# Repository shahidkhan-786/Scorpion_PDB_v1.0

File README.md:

# Scorpion_PDB_v1.0

I am making a Buck converter. 
I am making it using a TPS563200 Chip...I used ths because it is Small, Cheap, and Reliable to output 3A Current.

This is my schematic...I mostly referred to DataSheet of TPS563200.

This is the Layout/Routing part...I think this was the hardest part of the project, since the DataSheet gave very strict instructions for this.

Hopefully after soldering all components it look like this.

The sole purpose of the project is to power my Drone...or Future Drone : "Scorpion" ;)

Note : PDB translates to 'Power Distribution Board'

As the name suggests it will disribute power to all my Servo motors, ESC's, ESP32 (which i will be using for my Flight Controller for Scorpion) and/or any other Sensors
that I will be using in future...that's exactly why I have created 7 outputs...!

Here is the BOM of this PDB : 

This is Component Part.

This is PCB Part (I am ordering from JLCPCB).

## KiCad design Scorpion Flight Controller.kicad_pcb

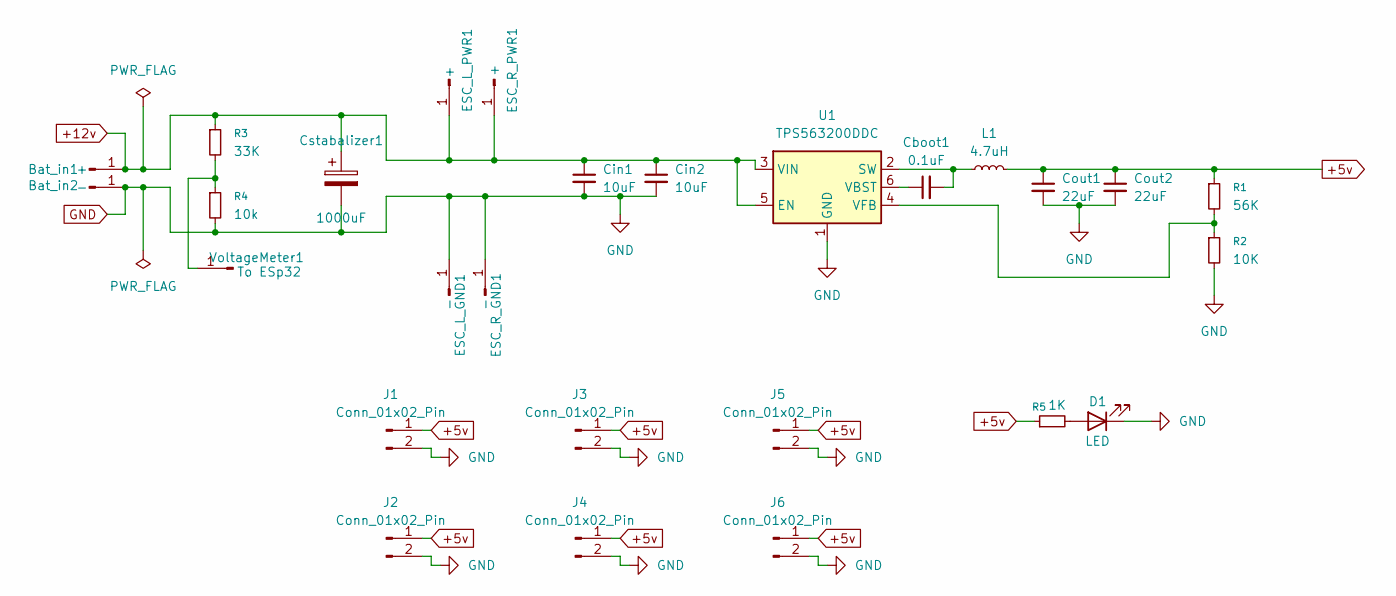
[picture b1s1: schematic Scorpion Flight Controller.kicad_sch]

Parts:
Bat_in1: +; TestPoint_Plated_Hole_D3.0mm
Bat_in2: -; TestPoint_Plated_Hole_D3.0mm
Cboot1: 0.1uF; C_0805_2012Metric_Pad1.18x1.45mm_HandSolder
Cin1, Cin2: 10uF; C_1206_3216Metric_Pad1.33x1.80mm_HandSolder
Cout1, Cout2: 22uF; C_1206_3216Metric_Pad1.33x1.80mm_HandSolder
Cstabalizer1: 1000uF; CP_Radial_D10.0mm_P5.00mm
D1: LED; LED_1206_3216Metric_Pad1.42x1.75mm_HandSolder
ESC_L_GND1: -; TestPoint_Pad_2.5x2.5mm
ESC_L_PWR1: +; TestPoint_Pad_2.5x2.5mm
ESC_R_GND1: -; TestPoint_Pad_2.5x2.5mm
ESC_R_PWR1: +; TestPoint_Pad_2.5x2.5mm
J1, J2, J3, J4, J5, J6: Conn_01x02_Pin; TestPoint_2Pads_Pitch5.08mm_Drill1.3mm
L1: 4.7uH; L_10.4x10.4_H4.8
R1: 56K; R_1206_3216Metric_Pad1.30x1.75mm_HandSolder
R2: 10K; R_1206_3216Metric_Pad1.30x1.75mm_HandSolder
R3: 33K; R_1206_3216Metric_Pad1.30x1.75mm_HandSolder
R4: 10k; R_1206_3216Metric_Pad1.30x1.75mm_HandSolder
R5: 1K; R_1206_3216Metric_Pad1.30x1.75mm_HandSolder
U1: TPS563200DDC; SOT-23-6
VoltageMeter1: To ESp32; TestPoint_THTPad_1.0x1.0mm_Drill0.5mm

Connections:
+5v: Cout1.1, Cout2.1, J1.1, J2.1, J3.1, J4.1, J5.1, J6.1, L1.2, R1.1, R5.1; also elsewhere on the board
+12v: Bat_in1.1, Cin1.1, Cin2.1, Cstabalizer1.1, ESC_L_PWR1.1, ESC_R_PWR1.1, R3.1, U1.3 (VIN), U1.5 (EN)
GND: Bat_in2.1, Cin1.2, Cin2.2, Cout1.2, Cout2.2, Cstabalizer1.2, D1.1 (K), ESC_L_GND1.1, ESC_R_GND1.1, J1.2, J2.2, J3.2, J4.2, J5.2, J6.2, R2.2, R4.2, U1.1 (GND); also elsewhere on the board
unnamed: D1.2 (A), R5.2
unnamed: Cboot1.2, L1.1, U1.2 (SW)
unnamed: Cboot1.1, U1.6 (VBST)
unnamed: R1.2, R2.1, U1.4 (VFB)
unnamed: R3.2, R4.1, VoltageMeter1.1

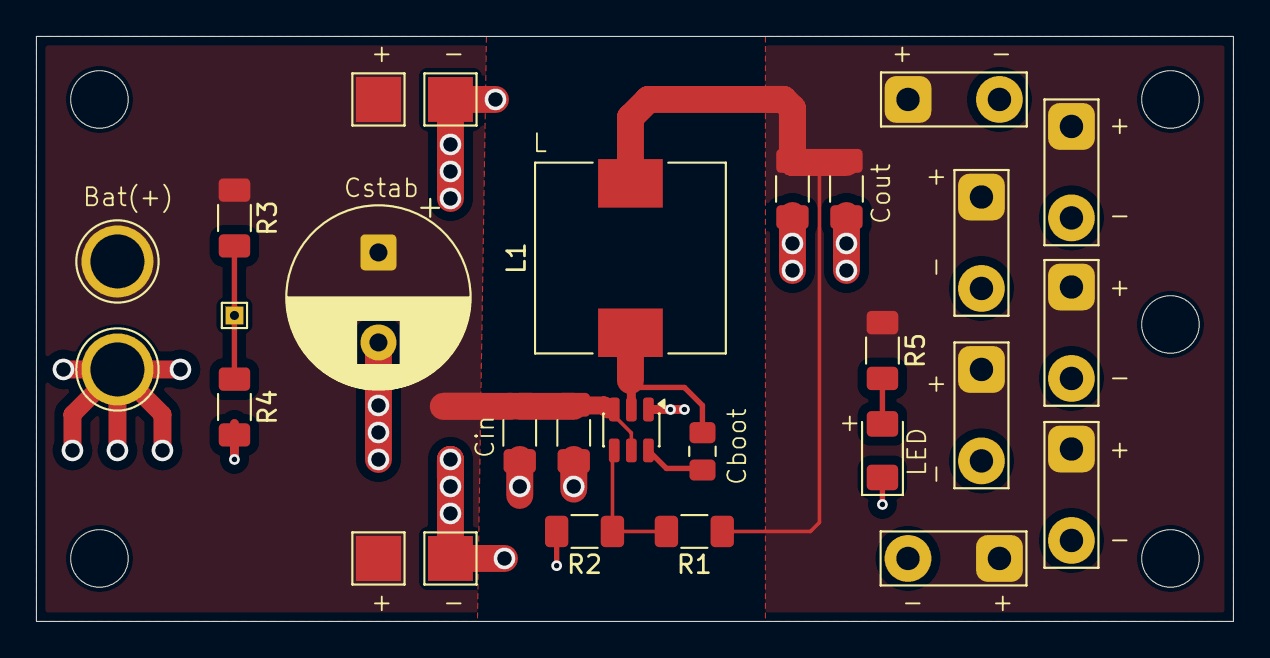
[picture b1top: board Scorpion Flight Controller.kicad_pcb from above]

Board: 2 copper layers, 66.5 x 32.5 mm, 28 parts (0 on the bottom side), 8 nets.

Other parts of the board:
J7: Conn_01x02_Pin; TestPoint_2Pads_Pitch5.08mm_Drill1.3mm

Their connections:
+5v: J7.1; also elsewhere on the board
GND: J7.2; also elsewhere on the board

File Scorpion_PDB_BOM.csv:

,,,,,,,
,,,,,,,
,,,,,,,
Item ,Description,Quantity,Unit Price (₹),Total Price (₹),URL,Running Total (₹),
,,,,,,,
TPS563200,Buck Chip,2,20,40,TPS563200DDCR-Texas Instruments-Step-down type Adjustable 760mV~7V 3A 4.5V~17V TSOT-23-6 DC-DC Converters ROHS,40,
4.7uH Inductor,Inductor,2,15,30,CDRH104R 4.7uH Power Inductor,70,
10uF Capacitor,Capacitor,5,7,35,CL31B106KBHNNNE-Samsung-50V 10uF X7R ±10% 1206 Multilayer Ceramic Capacitors MLCC - SMD/SMT ROHS,105,
22uF Capacitor,Capacitor,5,2.85,14.25,CL31A226KOHNNNE-Samsung-16V 22uF X5R ±10% 1206 Multilayer Ceramic Capacitors MLCC - SMD/SMT ROHS,119.25,
100nF Capacitor,Capacitor,15,0.72,10.8,CL21B104KBCNFNC-Samsung-50V 100nF X7R ±10% 0805 Multilayer Ceramic Capacitors MLCC - SMD/SMT ROHS,130.05,
1000uF Capacitor,Capacitor,2,15,30,"25YXJ1000MT810X20-Rubycon-1000uF 25V 46mΩ@100kHz ±20% 1.4A@100kHz Plugin,D10xL20mm Aluminum Electrolytic Capacitors - Leaded ROHS",160.05,
56k ohm Resistor,Resistor,30,0.35,10.5,"RC1206FR-0756KL-Yageo-SMD Chip Resistor, 56 kohm, ± 1%, 250 mW, 1206 [3216 Metric], Thick Film, General Purpose",170.55,
1k ohm Resistor,Resistor,25,0.46,11.5,RC1206FR-071KL-YAGEO-Res Thick Film 1206 1K Ohm 1% 0.25W(1/4W) ±100ppm/°C Pad SMD T/R,182.05,
33k ohm Resistor,Resistor,30,0.35,10.5,"RC1206FR-0733KL-Yageo-SMD Chip Resistor, 33 kohm, ± 1%, 250 mW, 1206 [3216 Metric], Thick Film, General Purpose",192.55,
10k ohm Resistor,Resistor,40,0.25,10,RC1206FR-0710KL-YAGEO-Res Thick Film 1206 10K Ohm 1% 0.25W(1/4W) ±100ppm/°C Pad SMD T/R,202.55,
LED,LED,15,0.92,13.8,1206 Surface Mount LED White,216.35,
XT-60,Connector,1,34,34,Amass XT60H Male Connector with Housing - XT60H-M.G.Y,250.35,
Holder,Battery Holder,1,39,39,4 x AA Battery Holder Box with 9V Battery Buckle without Cover （Back-to-Back）,289.35,
,,,,,,,
Shipping ,of Components, _,_,49,_,338.35,
Discount,_,_,_,1,_,337.35,
,,,,,,,
,,,,,,,
,,,,,,,
,,,,,,,
,,,,,,,
,,,,,,,
Item ,Quantity,Price ($),Running Total ($),,,,
,,,,,,,
PCB,5,2,2,,,,
Shipping,_,7.98,9.98,,,,
,,,,,,,
,,,,,,,
,,,,,,,
,,,,,,,

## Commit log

2026-01-02 Project Description
    Expanded project description and added images for schematic, layout, BOM, and components.
2026-01-02 Cart of JLCPCB
    This is screenshot of cart of JLCPCB
2026-01-02 Cart of Robu
    This is cart of robu...from where i buy components.
2026-01-02 This is BOM
    I have added both Components and PCB in this single file.
2026-01-03 Kicad Source files.
